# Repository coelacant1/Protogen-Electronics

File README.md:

# SmartMatrixProtogenShield
SmartMatrix SmartLED Shield breakout for Protogen hardware

## General Information
The SmartLED Shield for the Teensy 4 is used as the backbone to this design. This allows you to use open-source code to easily implement if you decide against using ProtoTracer to display graphics on your Protogen!

The following information is pulled directly from their Crowd Supply page as a means of maintaining a local copy in case they take the posting down:
[SmartLED Shield for Teensy 4](https://www.crowdsupply.com/pixelmatix/smartled-shield-for-teensy-4)

## Controller Breakout

### Information
The controller breakout provides sensor connectivity, power distribution, and indication methods for power.

## Bill of Materials

| **RefDes**     | **Value**     | **Footprint** | **Quantity** | **Description**                       |
|----------------|---------------|---------------|--------------|---------------------------------------|
| C1-C4          | 22µF          | SMD 0805      | 4            | Power filtering capacitors            |
| R1,R2,R5,R6    | 10KΩ          | SMD 0805      | 4            | Pull-up resistors                     |
| R3,R4          | 470Ω          | SMD 0805      | 2            | APA102 impedance matching resistors   |
| LED1-2         |               | SMD 0805      | 2            | Indicator LEDs. Type does not matter. |
| LEDPWR, BCKPWR | AMASS XT30UPB-F | Through-Hole  | 2            | Power in and out                      |
| I2C1-4         | JST S4B-XH-A  | Through-Hole  | 4            | I2C Devices                           |

## Power Setup

### Powering the Teensy 4.0 for Programming
For programming the Teensy 4.0, the bottom VIN from VUSB trace needs to be cut to not provide power to the LED boards and cause damage while programming.

### Powering the Controller for Usage
To use the controller, 5V must be provided to the XT30 connector. Make sure you follow the standards for the XT30 polarity!

## Sensors/Peripherals

### Boop Sensor (APDS-9960)
The APDS-9960 is a Time-of-Flight sensor that uses an IR light to measure the distance to the object in front of it using the I2C communication protocol. This can be connected on either the Teensy I2C breakout or the ESP32 I2C breakout. The following picture shows the recommended location for the device:

### MAX9814 Microphone
The MAX9814 electret microphone is a standard electret microphone with automatic gain compensation via an amplifier. This will pick up a varying range of sounds and not just your voice, so it is best to tune the software gain appropriately.

### Control Button
The control button is a simple button that allows you to toggle between faces. There is no analog filtering on the button with the kit as the button debouncing is handled in code within the ButtonHandler class.

### I2C OLED Display
The OLED display is a small display for mounting within the visor for the wearer to see. It is used to display the current face being displayed on the outside, status of a battery, or anything else you like. This will communicate over I2C with either the Teensy or the ESP32.

## Programming the Teensy

### Getting Started with ProtoTracer

#### Install Applications
- Install Visual Studio Code from here: [Visual Studio Code](https://code.visualstudio.com/)
- Install TeensyDuino from here: [TeensyDuino](https://www.pjrc.com/teensy/td_download.html)

#### Install Extensions
- Install PlatformIO IDE under the extensions in Visual Studio Code.
- Install C/C++ extension.

#### Download the Codebase
Download ProtoTracer from here: [ProtoTracer](https://github.com/coelacant1/ProtoTracer). You can use either the Zip download or clone it to a local Git repository.

## General Recommendations and Notes
- Do not use external power to the XT30 connector, unless it is 5V directly, the controller should be able to handle 4.5V to 5.5V but anything else is outside of specification.
- Do not short circuit the IO pins. Be careful about which pins are in use and are listed at the beginning of the guide.
- Be careful leaving the electronics in a humid environment.

## Images

### 3D View

### 3D View with Components

### Layer View

### Electrical Schematic

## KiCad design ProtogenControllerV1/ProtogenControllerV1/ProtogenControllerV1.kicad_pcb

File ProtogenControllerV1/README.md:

# ProtogenControllerV1
Protogen Controller V1 with Bluetooth

## General Information
This controller is used to control up to 8 WS2812 strips at 500 pixels long each. This supports an ESP32 WROVER used for communication to other wireless devices that talks to the Teensy 4.0 over Serial. Both devices have breakouts for I2C and SPI as well as all unused GPIO. The ESP32 is programmed over USB using the integrated CP2104 FTDI.

## Bill of Materials

| **RefDes**                                   | **Value**           | **Footprint** | **Quantity** | **Description**                                                                                       |
|----------------------------------------------|---------------------|---------------|--------------|-------------------------------------------------------------------------------------------------------|
| C1, C2, C3, C4, C5, C6, C7, C8, DC1, DC2, DC3, DC4, DC5, DC6, DC7, DC8 | CC0805KKX7R6BB105 | 0805          | 16           | CAP CER 1UF 10V X7R                                                           |
| J1                                           | 47589-0001          |               | 1            | Right Angle Female Type AB Micro USB Connector, 30 V, 1.8 A, -30 to 85 degC, RoHS, Tape and Reel      |
| J1_JSTBreakout1, J1_JSTBreakout2, J1_JSTBreakout3, J1_JSTBreakout4, J1_JSTBreakout5, J1_JSTBreakout6, J1_JSTBreakout7, J1_JSTBreakout8 | B3B-XH-A(LF)(SN) | 2.5MM         | 8            | CONN HEADER VERT 3POS |
| J2                                           | XT30-F              |               | 1            | XT30 Female connector for board mount                                                                 |
| LED1, LED2, LED3                             | 150080SS75000       |               | 3            | SMD mono-color Chip LED, WL-SMCW, Super Red                                                           |
| P1                                           | Header 16X2         |               | 1            | Header, 16-Pin, Dual row                                                                              |
| P2, P3                                       | Header 4X2          |               | 2            | Header, 4-Pin, Dual row                                                                               |
| P4, P5                                       | Header 6X2          |               | 2            | Header, 6-Pin, Dual row                                                                               |
| P6                                           | Header 2            |               | 1            | Header, 2-Pin                                                                                         |
| Q1, Q2                                       | MMBT2222ALT1G       | SOT-23        | 2            | General Purpose Transistor, NPN Silicon, 3-Pin, Pb-Free, Tape and Reel                                |
| Q3                                           | FDN339AN            | SSOT3         | 1            | MOSFET N-CH 20V 3A                                                                                    |
| Q4                                           | FDN340P             | SSOT3         | 1            | MOSFET P-CH 20V 2A                                                                                    |
| R1, R2, R3, R4, R5, R6, R9, R10, R14, R15, R16, R17, R18, R19, R20 | CRCW08050000Z0EA  |               | 15           |                                                                                   |
| R7, R8, R13                                  | CAT16-103J4LF       | 8-Pin SMD     | 3            | CAT / CAY 16 Series - Chip Resistor Array, 10 KOhm, +/- 5%, 50 V, -55 to 125 degC, RoHS, Tape and Reel |
| SW1                                          | FSMSMTR             | 2-Pin SMD     | 1            | FSMSM Push Button Switch, 50 mA, -35 to 85 degC, RoHS, Tape and Reel                                  |
| U1                                           | ESP32-WROVER-B_(16MB)|               | 1            | Generic WiFi-BT-BLE MCU module. Flash memory of 16 MB and PSRAM of 8 MB                              |
| U2                                           | Teensy 4.0          |               | 1            | RT1062 Teensy 4.0 i.MX ARM® Cortex®-M7 MPU Embedded Evaluation Board                                  |
| U4                                           | AP2112K-3.3TRG1     | SOT25         | 1            | IC REG LINEAR 3.3V 600MA                                                                              |
| U5                                           | CP2104-F03-GM       | 24-pin QFN    | 1            | Single-Chip USB to UART Bridge, 4 Dig I/O Pins, Internal Oscillator, 1024 Bytes EEPROM, -40 to 85 degC|
| U6                                           | SN74HCT245DWR       | 20SOIC        | 1            | IC TXRX NON-INVERT 5.5V                                                                               |

## Power Setup

### Powering the Teensy 4.0 for Programming
For programming the Teensy 4.0, the bottom VIN from VUSB trace needs to be cut to not provide power to the LED boards and cause damage while programming.

### Powering the Controller for Usage
To use the controller, 5V must be provided to the XT30 connector. Make sure you follow the standards for the XT30 polarity!

## Sensors/Peripherals

### Boop Sensor (APDS-9960)
The APDS-9960 is a Time-of-Flight sensor that uses an IR light to measure the distance to the object in front of it using the I2C communication protocol. This can be connected on either the Teensy I2C breakout or the ESP32 I2C breakout. The following picture shows the recommended location for the device:

### MAX9814 Microphone
The MAX9814 electret microphone is a standard electret microphone with automatic gain compensation via an amplifier. This will pick up a varying range of sounds and not just your voice, so it is best to tune the software gain appropriately.

### Control Button
The control button is a simple button that allows you to toggle between faces. There is no analog filtering on the button with the kit as the button debouncing is handled in code within the ButtonHandler class.

### I2C OLED Display
The OLED display is a small display for mounting within the visor for the wearer to see. It is used to display the current face being displayed on the outside, status of a battery, or anything else you like. This will communicate over I2C with either the Teensy or the ESP32.

## Programming the Teensy

### Getting Started with ProtoTracer

#### Install Applications
- Install Visual Studio Code from here: [Visual Studio Code](https://code.visualstudio.com/)
- Install TeensyDuino from here: [TeensyDuino](https://www.pjrc.com/teensy/td_download.html)

#### Install Extensions
- Install PlatformIO IDE under the extensions in Visual Studio Code.
- Install C/C++ extension.

#### Download the Codebase
Download ProtoTracer from here: [ProtoTracer](https://github.com/coelacant1/ProtoTracer). You can use either the Zip download or clone it to a local Git repository.

## General Recommendations and Notes
- Do not use external power to the XT30 connector, unless it is 5V directly, the controller should be able to handle 4.5V to 5.5V but anything else is outside of specification.
- Do not short circuit the IO pins. Be careful about which pins are in use and are listed at the beginning of the guide.
- Be careful leaving the electronics in a humid environment.

## Images

### 3D View

### Wiring

### Layer View

### Electrical Schematic

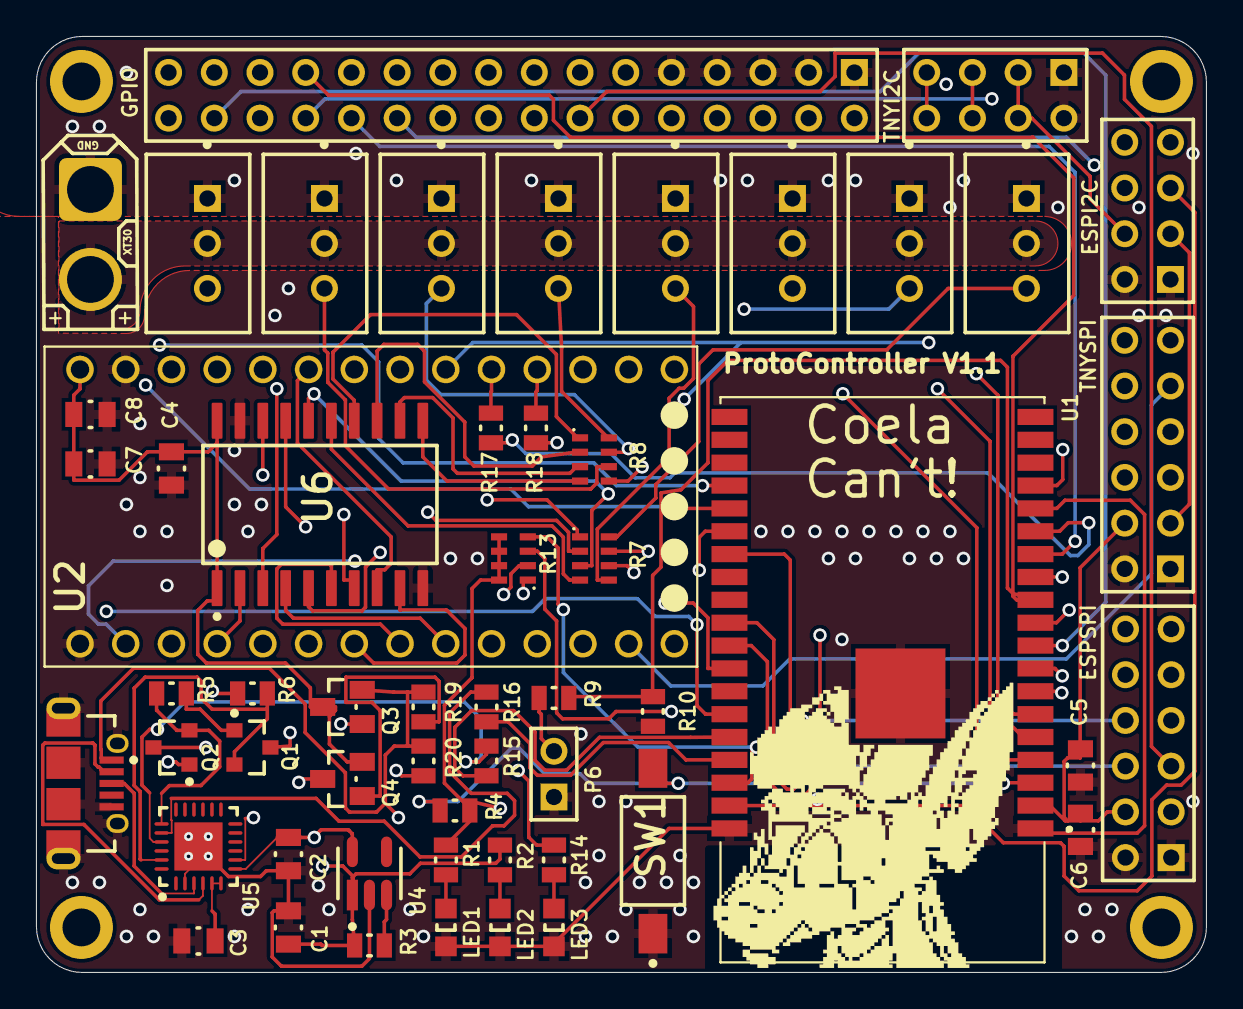
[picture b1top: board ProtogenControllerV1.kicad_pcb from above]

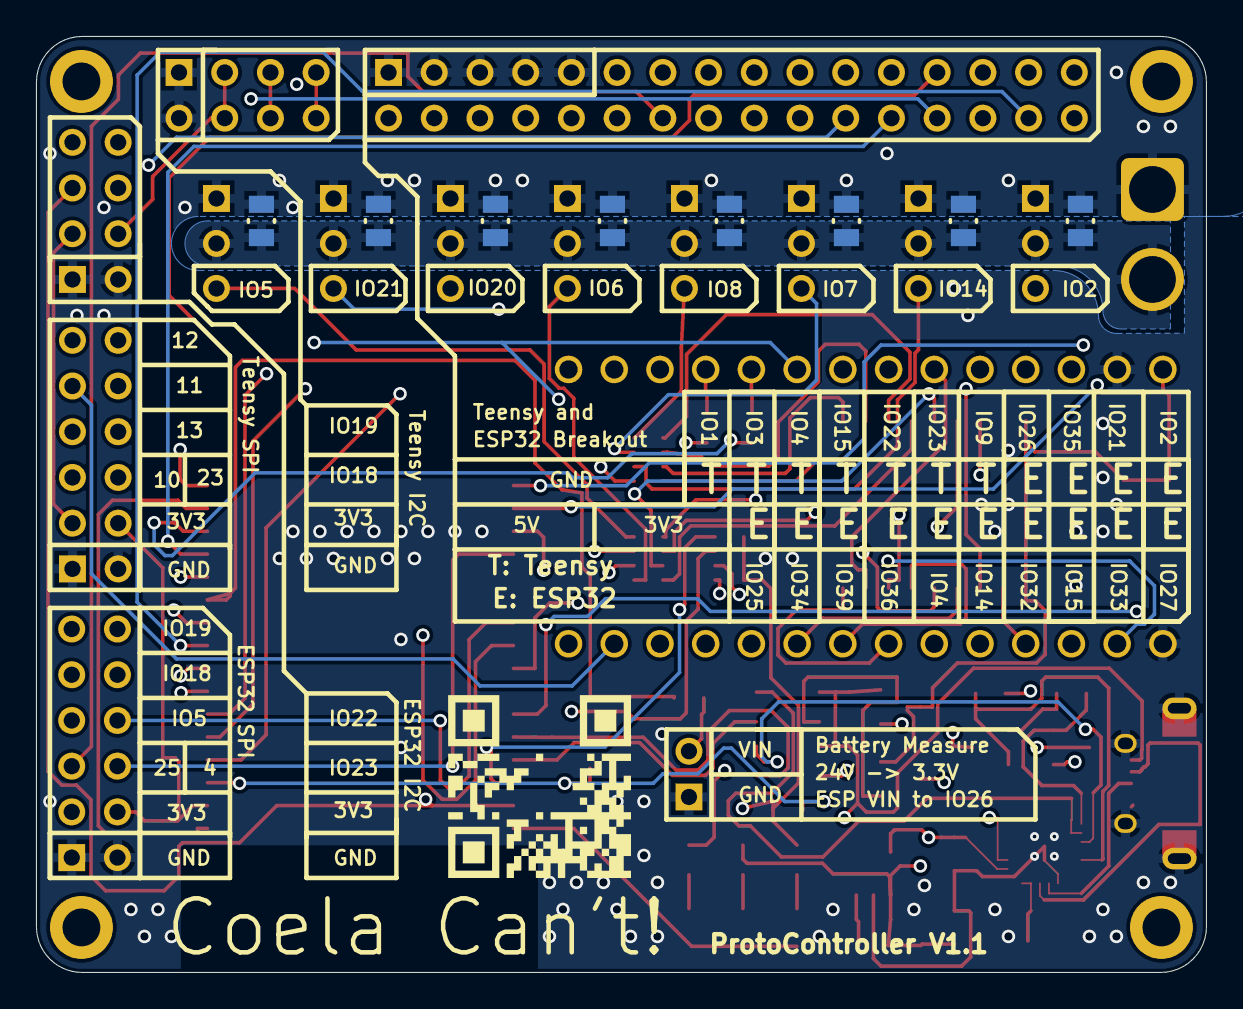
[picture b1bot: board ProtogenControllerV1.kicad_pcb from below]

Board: 4 copper layers, 65.0 x 52.0 mm, 62 parts (8 on the bottom side), 84 nets.

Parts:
C1, C2, C3, C4, C5, C6, C7, C8: CC0805KKX7R6BB105; FP-CC0805-0_85-MFG
DC1, DC2, DC3, DC4, DC5, DC6, DC7, DC8: CC0805KKX7R6BB105; FP-CC0805-0_85-MFG
ESPSPI: Header 6X2; HDR2X6
GPIO: Header 16X2; HDR2X16
J1_JSTBreakout1, J1_JSTBreakout2, J1_JSTBreakout3, J1_JSTBreakout4, J1_JSTBreakout5, J1_JSTBreakout6, J1_JSTBreakout7, J1_JSTBreakout8: B3B-XH-A(LF)(SN); FP-B3B-XH-A_LF_SN-MFG
J2: XT30-F; XT30-F-Footprint-1
LED1, LED2, LED3: 150080SS75000; 0805_A
P2, P3: Header 4X2; HDR2X4
P6: Header 2; HDR1X2
Q1, Q2: MMBT2222ALT1G; ONSC-SOT-23-3-318-08_V
Q3: FDN339AN; FP-527AG-MFG
Q4: FDN340P; FP-527AG-MFG
R1, R2, R3, R4, R5, R6, R9, R10, R14, R15, R16, R17, R18, R19, R20: CRCW08050000Z0EA; RESC2013X50X30LL20T20
R7, R8, R13: CAT16-103J4LF; BOUR-CAT16-103J4LF_L
SW1: FSMSMTR; TECO-FSMSMTR_V
TNYSPI: Header 6X2; HDR2X6
U1: ESP32-WROVER-B_(16MB); XCVR_ESP32-WROVER-B_(16MB)
U2: Teensy 4.0; MODULE_DEV-15583
U4: AP2112K-3.3TRG1; FP-SOT25-IPC_A
U5: CP2104-F03-GM; SLAB-QFN-24-2675x2675TP_M
U6: SN74HCT245DWR; FP-DW0020A-MFG

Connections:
+3V3: C2.2, C5.1, C6.1, ESPSPI.3, ESPSPI.4, GPIO.8, GPIO.10, GPIO.12, P2.3, P2.4, P3.3, P3.4, R1.1, R4.1, R13.5, R13.6, R13.7, R13.8, TNYSPI.3, TNYSPI.4, U1.2, U4.5, U5.7
+5: C1.1, C4.2, C7.1, C8.1, GPIO.2, GPIO.4, GPIO.6, Q3.3, Q4.2, R2.1, R3.2, U2.VIN, U4.1, U6.1, U6.20
A1_2: U2.2, U6.2
A2_14: U2.14, U6.3
A3_7: U2.7, U6.4
A4_8: U2.8, U6.5
A5_6: U2.6, U6.6
A6_20: U2.20, U6.7
A7_21: U2.21, U6.8
A8_5: U2.5, U6.9
DIN1: J1_JSTBreakout1.3, R7.8
DIN2: J1_JSTBreakout2.3, R7.7
DIN3: J1_JSTBreakout3.3, R7.6
DIN4: J1_JSTBreakout4.3, R7.5
DIN5: J1_JSTBreakout5.3, R8.8
DIN6: J1_JSTBreakout6.3, R8.7
DIN7: J1_JSTBreakout7.3, R8.6
DIN8: J1_JSTBreakout8.3, R8.5
GND: C1.2, C2.1, C3.2, C4.1, C5.2, C6.2, C7.2, C8.2, DC1.2, DC2.2, DC3.2, DC4.2, DC5.2, DC6.2, DC7.2, DC8.2, ESPSPI.1, ESPSPI.2, GPIO.1, GPIO.3, GPIO.5, GPIO.7, GPIO.9, J1_JSTBreakout1.1, J1_JSTBreakout2.1, J1_JSTBreakout3.1, J1_JSTBreakout4.1, J1_JSTBreakout5.1, J1_JSTBreakout6.1, J1_JSTBreakout7.1, J1_JSTBreakout8.1, J2.1, LED1.1, LED2.1, LED3.1, P2.1, P2.2, P3.1, P3.2, P6.1, R10.2, SW1.1, TNYSPI.1, TNYSPI.2, U1.1, U1.15, U1.38, U1.39, U2.G1, U2.G3, U4.2, U5.2, U5.25, U6.10, U6.19
NetC3_1: C3.1, U5.5, U5.6
NetLED1_2: LED1.2, R1.2
NetLED2_2: LED2.2, R2.2
NetLED3_2: LED3.2, R14.2
NetP1_11: GPIO.11, U2.0
NetP1_13: GPIO.13, U2.1
NetP1_14: ESPSPI.5, GPIO.14, U1.10
NetP1_15: GPIO.15, U2.3
NetP1_16: GPIO.16, U1.6
NetP1_17: GPIO.17, U2.4
NetP1_18: GPIO.18, U1.5
NetP1_19: GPIO.19, U2.15
NetP1_20: GPIO.20, U1.4
NetP1_21: GPIO.21, U2.22
NetP1_22: ESPSPI.6, GPIO.22, U1.26
NetP1_23: GPIO.23, U2.23
NetP1_24: GPIO.24, U1.13
NetP1_25: GPIO.25, R9.2, R10.1, U1.11
NetP1_26: GPIO.26, U1.8
NetP1_27: GPIO.27, R14.1, U1.7
NetP1_28: GPIO.28, U1.23
NetP1_29: GPIO.29, U1.33
NetP1_30: GPIO.30, U1.9
NetP1_31: GPIO.31, U1.24
NetP1_32: GPIO.32, U1.12
NetP2_5: P2.5, P2.6, R13.2, U2.18
NetP2_7: P2.7, P2.8, R13.1, U2.19
NetP3_5: P3.5, P3.6, R13.3, U1.37
NetP3_7: P3.7, P3.8, R13.4, U1.36
NetP4_5: TNYSPI.5, U2.10
NetP4_6: TNYSPI.6, U2.9
NetP4_7: TNYSPI.7, TNYSPI.8, U2.13
NetP4_9: TNYSPI.9, TNYSPI.10, U2.11
NetP4_11: TNYSPI.11, TNYSPI.12, U2.12
NetP5_7: ESPSPI.7, ESPSPI.8, U1.29
NetP5_9: ESPSPI.9, ESPSPI.10, U1.30
NetP5_11: ESPSPI.11, ESPSPI.12, U1.31
NetQ1_1: Q1.1, R5.2
NetQ1_2: Q1.2, R6.1, U5.23
NetQ1_3: Q1.3, U1.25
NetQ2_1: Q2.1, R6.2
NetQ2_2: Q2.2, R5.1, U5.19
NetQ2_3: Q2.3, R4.2, SW1.2, U1.3
NetQ3_1: Q3.1, R20.1
NetQ4_1: Q4.1, R19.1
NetR3_1: R3.1, U4.3
NetR7_1: R7.1, U6.18
NetR7_2: R7.2, U6.17
NetR7_3: R7.3, U6.16
NetR7_4: R7.4, U6.15
NetR8_1: R8.1, U6.14
NetR8_2: R8.2, U6.13
NetR8_3: R8.3, U6.12
NetR8_4: R8.4, U6.11
NetR15_1: R15.1, U5.21
NetR15_2: R15.2, U1.34
NetR16_1: R16.1, U5.20
NetR16_2: R16.2, U1.35
NetR17_1: R17.1, U2.17
NetR17_2: R17.2, U1.14
NetR18_1: R18.1, U2.16
NetR18_2: R18.2, U1.16
VBCK: DC1.1, DC2.1, DC3.1, DC4.1, DC5.1, DC6.1, DC7.1, DC8.1, J1_JSTBreakout1.2, J1_JSTBreakout2.2, J1_JSTBreakout3.2, J1_JSTBreakout4.2, J1_JSTBreakout5.2, J1_JSTBreakout6.2, J1_JSTBreakout7.2, J1_JSTBreakout8.2, J2.2, Q4.3
VIN: P6.2, R9.1
VUSB: Q3.2, R19.2, R20.2, U5.8

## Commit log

2025-01-01 Merged Protogen electronics repositories
2026-03-09 Added WS35 LED board Gerber files
